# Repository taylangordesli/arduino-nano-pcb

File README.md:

# arduino-nano-pcb
An entrance level project for PCB design with Arduino Nano.

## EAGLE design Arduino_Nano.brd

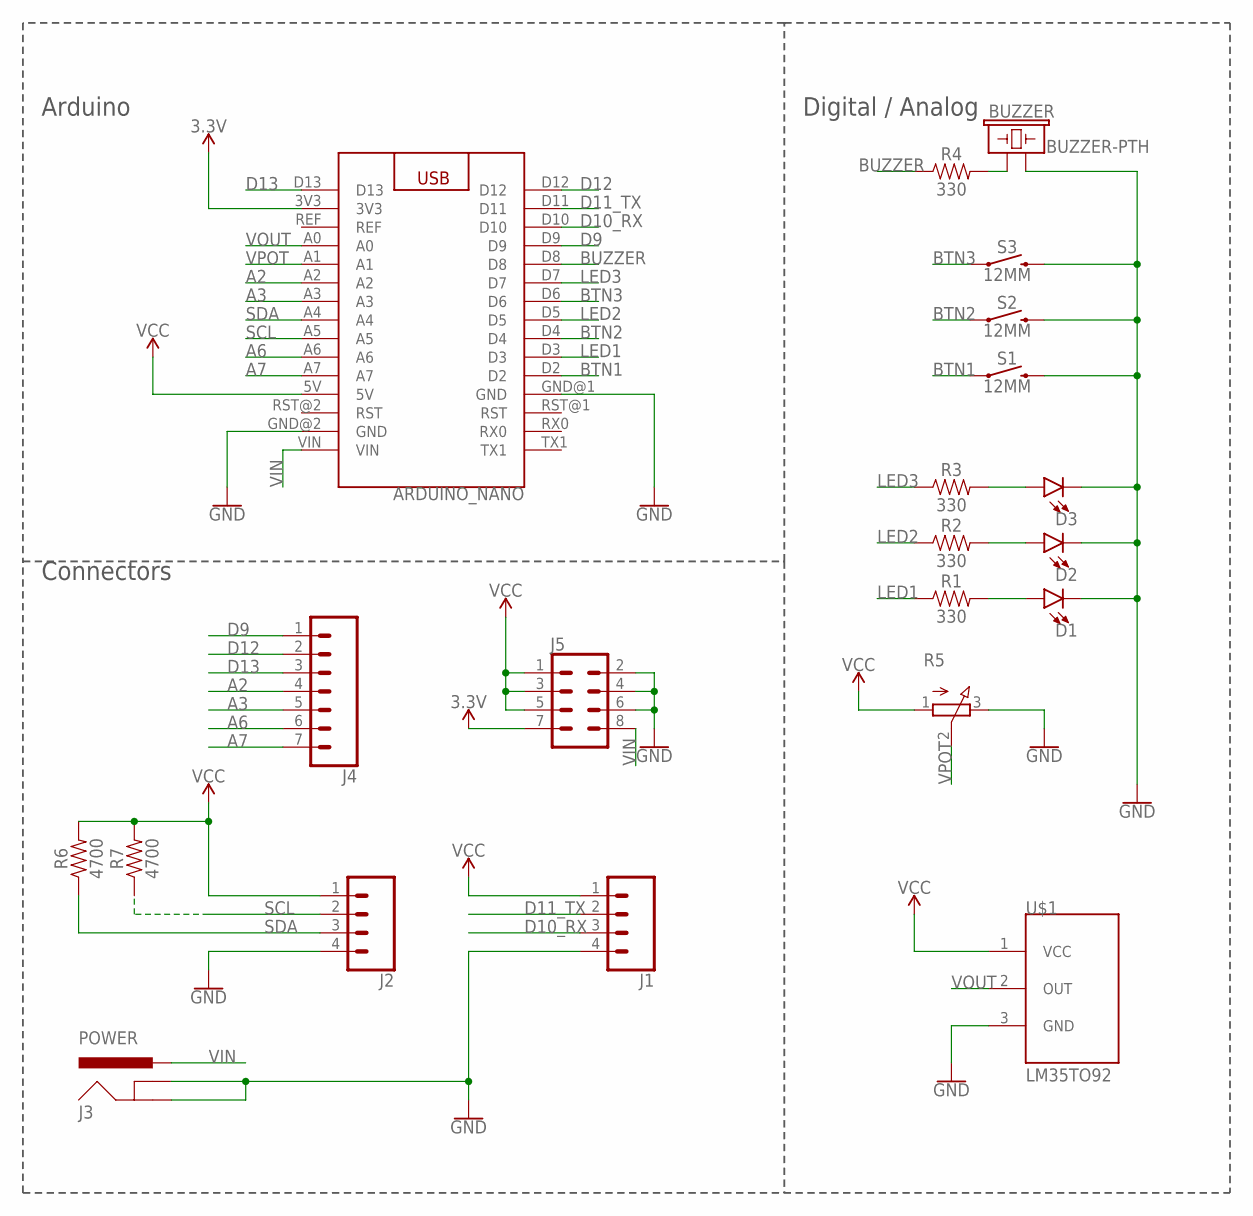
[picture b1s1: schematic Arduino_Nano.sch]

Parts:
ARDUINO_NANO: ARDUINO_NANO
BUZZER: BUZZER-PTH; BUZZER-12MM
D1, D2, D3: LED-3MM-NO_SILK; LED_3MM-NS
J1, J2: CONN_04PTH; 1X04
J3: POWER; POWER_JACK_PTH
J4: CONN_07; 1X07
J5: CONN_04X2; 2X4
R1, R2, R3, R4: 330; AXIAL-0.3
R5: 3RP/1610N
R6, R7: 4700; AXIAL-0.3
S1, S2, S3: 12MM; TACTILE_SWITCH_PTH_12MM
U$1: LM35TO92

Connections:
3.3V: ARDUINO_NANO.3V3, J5.7
A2: ARDUINO_NANO.A2, J4.4
A3: ARDUINO_NANO.A3, J4.5
A6: ARDUINO_NANO.A6, J4.6
A7: ARDUINO_NANO.A7, J4.7
BTN1: ARDUINO_NANO.D2, S1.1
BTN2: ARDUINO_NANO.D4, S2.1
BTN3: ARDUINO_NANO.D6, S3.1
BUZZER: ARDUINO_NANO.D8, R4.P$1 (1)
D9: ARDUINO_NANO.D9, J4.1
D10_RX: ARDUINO_NANO.D10, J1.3
D11_TX: ARDUINO_NANO.D11, J1.2
D12: ARDUINO_NANO.D12, J4.2
D13: ARDUINO_NANO.D13, J4.3
GND: ARDUINO_NANO.GND@2 (GND), BUZZER.- (2), D1.K (C), D2.K (C), D3.K (C), J1.4, J2.4, J3.GND, J3.GNDBREAK, J5.2, J5.4, J5.6, R5.3 (E), S1.3 (2), S2.3 (2), S3.3 (2), U$1.3 (GND)
LED1: ARDUINO_NANO.D3, R1.P$1 (1)
LED2: ARDUINO_NANO.D5, R2.P$1 (1)
LED3: ARDUINO_NANO.D7, R3.P$1 (1)
unnamed: BUZZER.+ (1), R4.P$2 (2)
unnamed: D3.A, R3.P$2 (2)
unnamed: D2.A, R2.P$2 (2)
unnamed: D1.A, R1.P$2 (2)
SCL: ARDUINO_NANO.A5, J2.2, R7.P$1 (1)
SDA: ARDUINO_NANO.A4, J2.3, R6.P$1 (1)
VCC: ARDUINO_NANO.5V, J1.1, J2.1, J5.1, J5.3, J5.5, R5.1 (A), R6.P$2 (2), R7.P$2 (2), U$1.1 (VCC)
VIN: ARDUINO_NANO.VIN, J3.PWR, J5.8
VOUT: ARDUINO_NANO.A0, U$1.2 (OUT)
VPOT: ARDUINO_NANO.A1, R5.2 (S)

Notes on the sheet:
Arduino
Connectors
Digital / Analog

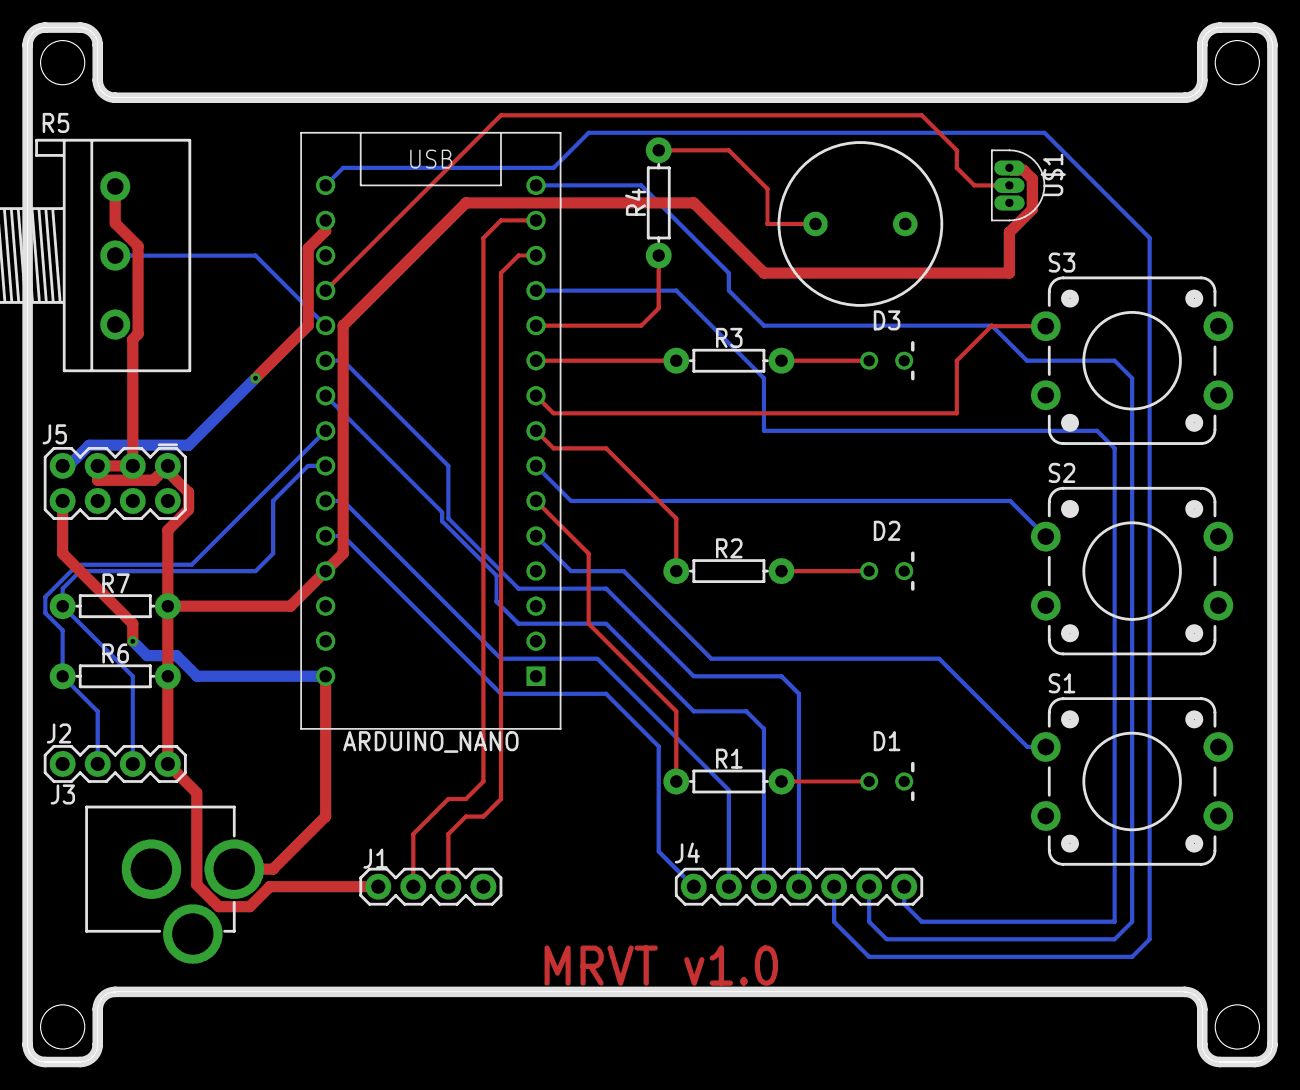
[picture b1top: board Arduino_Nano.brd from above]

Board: 2 copper layers, 90.2 x 74.9 mm, 21 parts (0 on the bottom side), 28 nets.

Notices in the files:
parts and their libraries:
SparkFun-LED: Licensing: Creative Commons ShareAlike 4.0 International - https://creativecommons.org/licenses/by-sa/4.0
